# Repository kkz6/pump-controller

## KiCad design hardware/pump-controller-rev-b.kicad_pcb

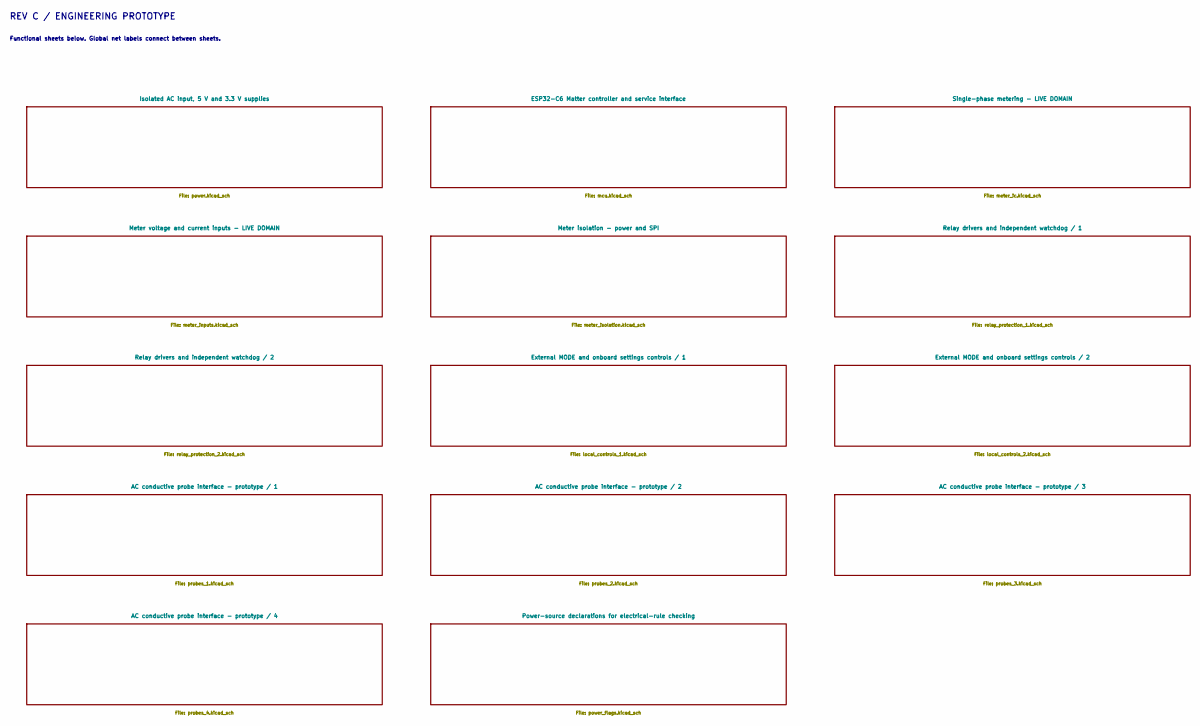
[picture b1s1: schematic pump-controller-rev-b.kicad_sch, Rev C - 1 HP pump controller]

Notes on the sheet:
REV C / ENGINEERING PROTOTYPE
Functional sheets below. Global net labels connect between sheets.

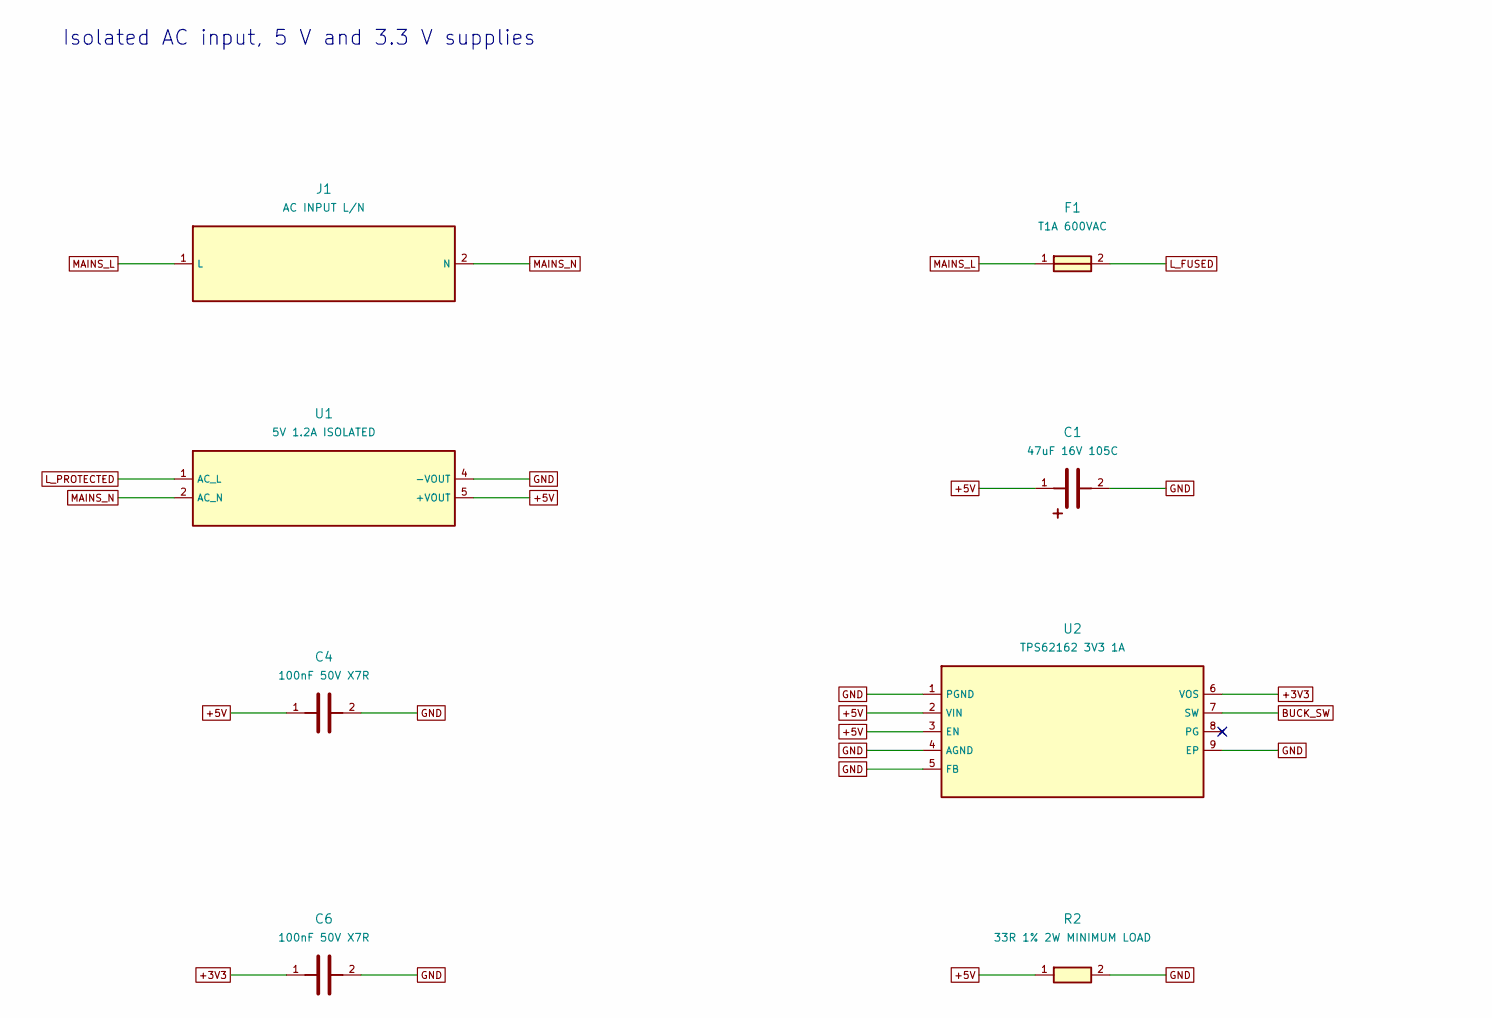
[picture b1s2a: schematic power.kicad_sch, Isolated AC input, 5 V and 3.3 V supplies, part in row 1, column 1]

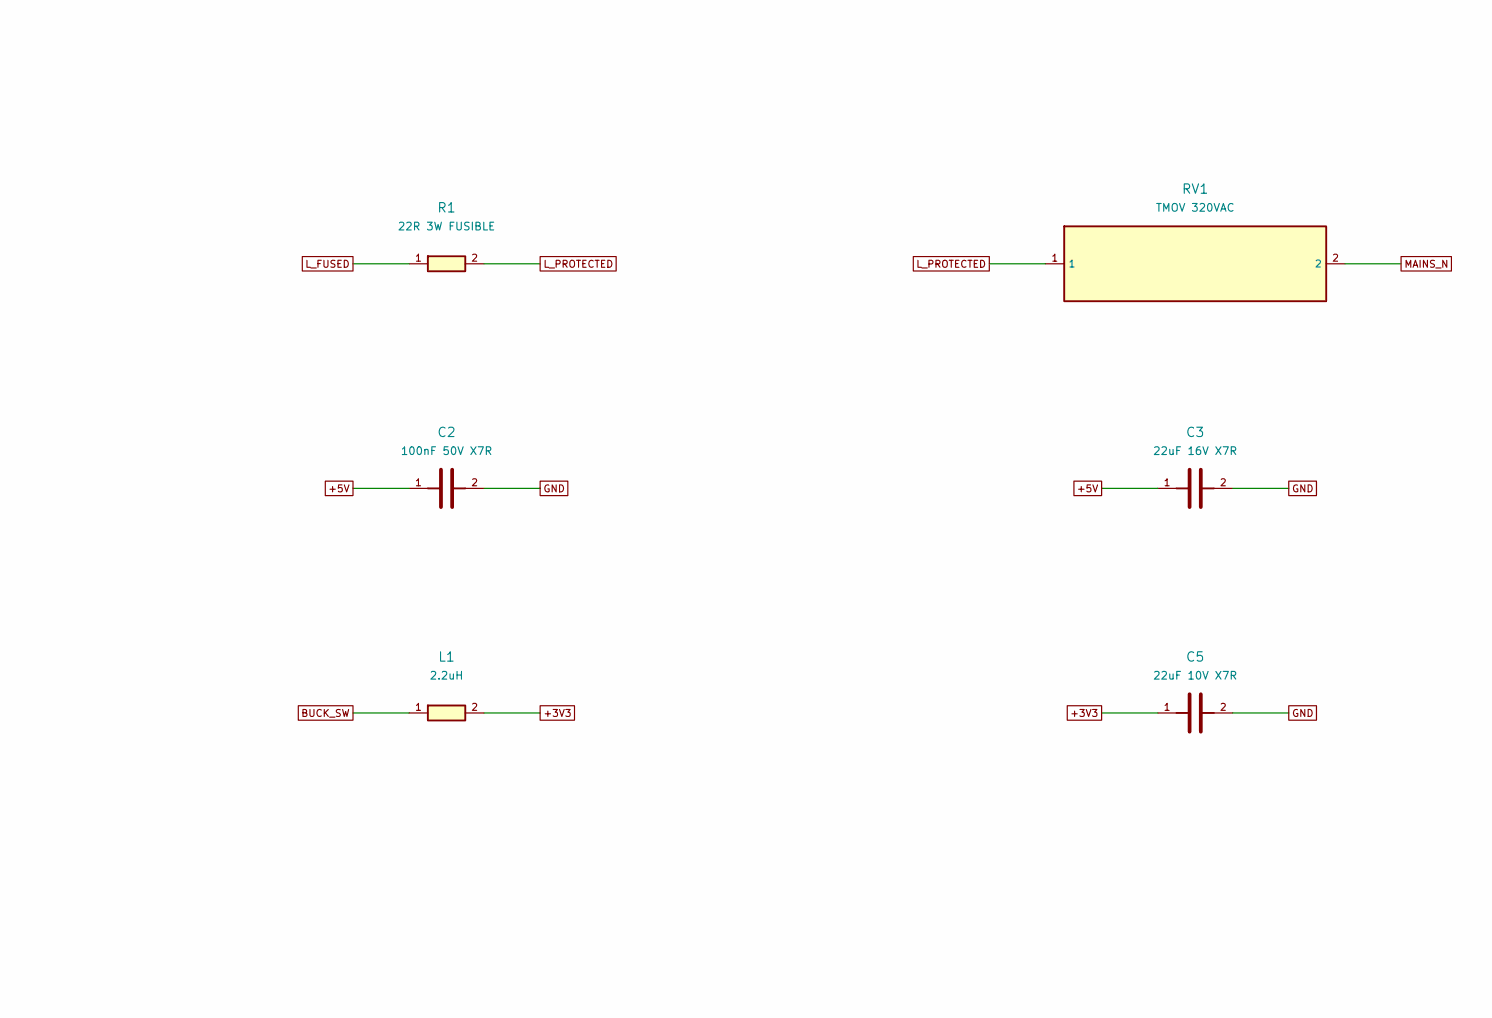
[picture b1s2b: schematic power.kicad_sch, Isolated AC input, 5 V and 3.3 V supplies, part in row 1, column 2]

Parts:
C1: 47uF 16V 105C; CP_Radial_D5.0mm_P2.00mm; MPN Generic 47uF 16V 105C low-impedance ele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
C2, C4, C6: 100nF 50V X7R; C_0805_2012Metric; MPN Generic 100nF 50V X7R 0805
C3: 22uF 16V X7R; C_1210_3225Metric; MPN Generic 22uF 16V X7R 1210
C5: 22uF 10V X7R; C_1210_3225Metric; MPN Generic 22uF 10V X7R 1210
F1: T1A 600VAC; Fuse_Axial_5x20_P27.94; MPN 0ADKP1000-RE
J1: AC INPUT L/N; TerminalBlock_Phoenix_MKDS-1,5-2-5.08_1x02_P5.08mm_Horizont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; MPN 1715721
L1: 2.2uH; L_Wuerth_MAPI-4030; MPN 74438357022
R1: 22R 3W FUSIBLE; R_Axial_L13_D6_P20.32; MPN AC03000002209JACCS
R2: 33R 1% 2W MINIMUM LOAD; R_2512_6332Metric; MPN CRM2512-FX-33R0ELF
RV1: TMOV 320VAC; TMOV14_Inline_P7.5; MPN TMOV14RP320EL2B7
U1: 5V 1.2A ISOLATED; RACM06E; MPN RACM06E-05SK/277
U2: TPS62162 3V3 1A; Texas_DSG0008A_WSON-8-1EP_2x2mm_P0.5mm_EP0.9x1.6mm_ThermalV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; MPN TPS62162DSGR

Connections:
+3V3: C5.1, C6.1, L1.2, U2.6 (VOS); also elsewhere on the board
+5V: C1.1, C2.1, C3.1, C4.1, R2.1, U1.5 (+VOUT), U2.2 (VIN), U2.3 (EN); also elsewhere on the board
BUCK_SW: L1.1, U2.7 (SW)
GND: C1.2, C2.2, C3.2, C4.2, C5.2, C6.2, R2.2, U1.4 (-VOUT), U2.1 (PGND), U2.4 (AGND), U2.5 (FB), U2.9 (EP); also elsewhere on the board
L_FUSED: F1.2, R1.1
L_PROTECTED: R1.2, RV1.1, U1.1 (AC_L); also elsewhere on the board
MAINS_L: F1.1, J1.1 (L)
MAINS_N: J1.2 (N), RV1.2, U1.2 (AC_N); also elsewhere on the board

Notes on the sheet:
Isolated AC input, 5 V and 3.3 V supplies

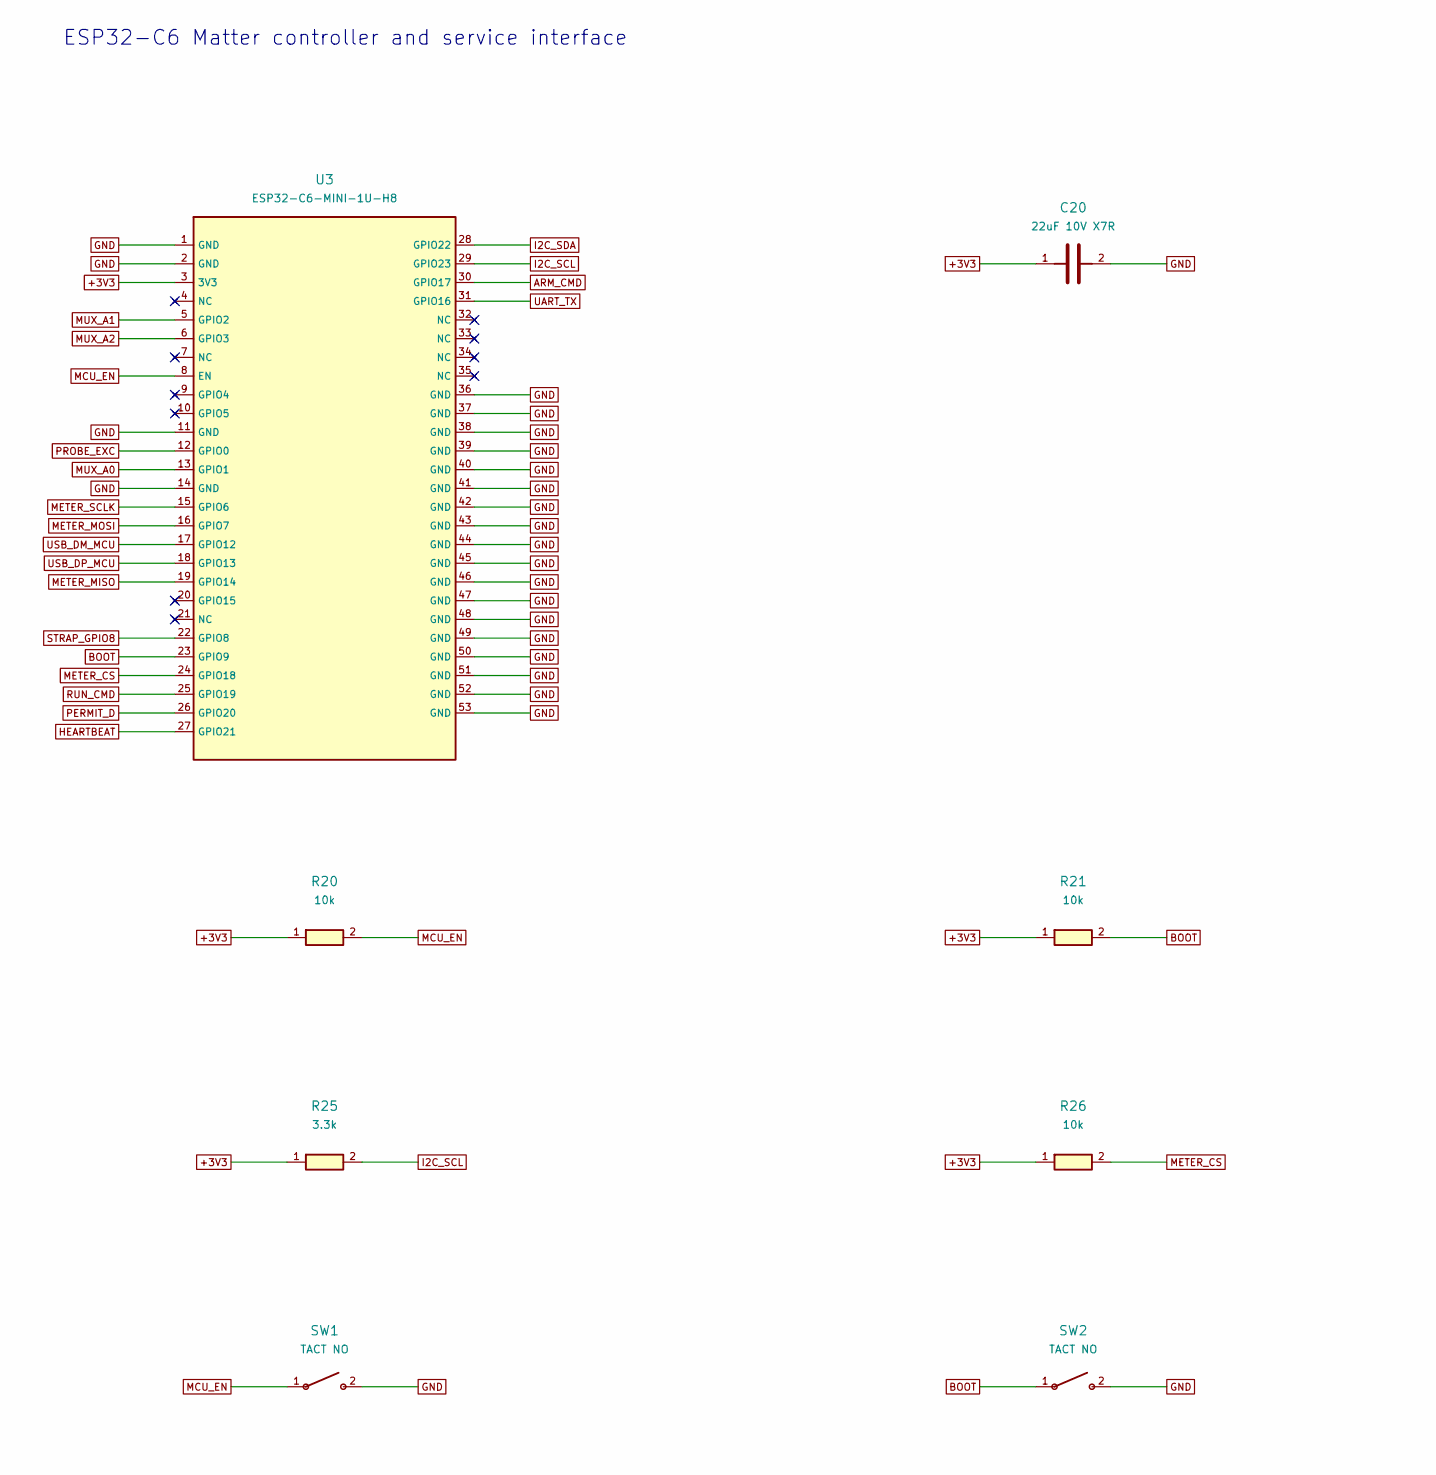
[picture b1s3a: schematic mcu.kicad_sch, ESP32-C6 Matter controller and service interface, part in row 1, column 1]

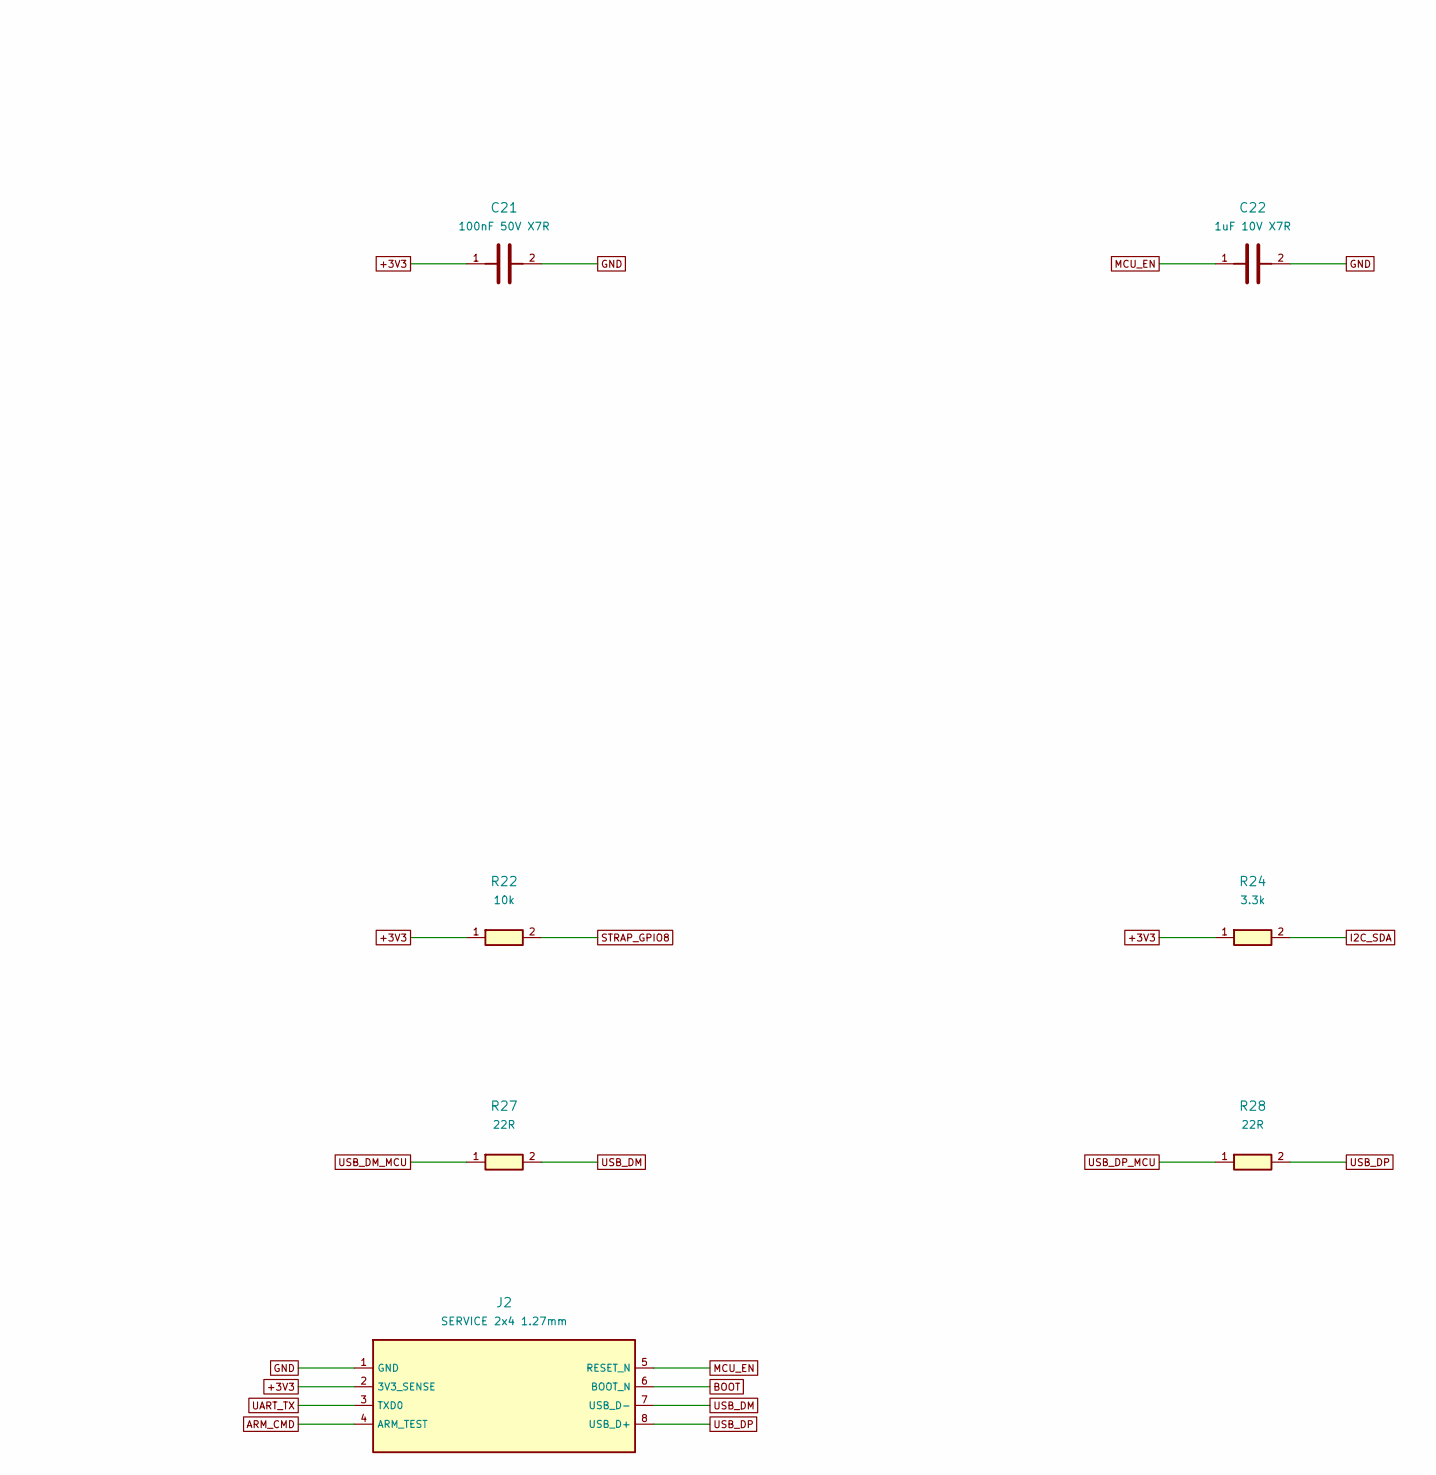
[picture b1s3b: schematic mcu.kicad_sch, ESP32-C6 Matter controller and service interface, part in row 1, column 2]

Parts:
C20: 22uF 10V X7R; C_1210_3225Metric; MPN Generic 22uF 10V X7R 1210
C21: 100nF 50V X7R; C_0805_2012Metric; MPN Generic 100nF 50V X7R 0805
C22: 1uF 10V X7R; C_0805_2012Metric; MPN Generic 1uF 10V X7R 0805
J2: SERVICE 2x4 1.27mm; PinHeader_2x04_P1.27mm_Vertical; MPN Generic 2x4 1.27 mm vertical male header
R20, R21, R22, R26: 10k; R_0805_2012Metric; MPN Generic 10k 1% 0.125 W 0805
R24, R25: 3.3k; R_0805_2012Metric; MPN Generic 3.3k 1% 0.125 W 0805
R27, R28: 22R; R_0805_2012Metric; MPN Generic 22R 1% 0.125 W 0805
SW1, SW2: TACT NO; SW_SPST_TL3305A; MPN TL3305AF160QG
U3: ESP32-C6-MINI-1U-H8; ESP32-C6-MINI-1U; MPN ESP32-C6-MINI-1U-H8

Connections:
+3V3: C20.1, C21.1, J2.2 (3V3_SENSE), R20.1, R21.1, R22.1, R24.1, R25.1, R26.1, U3.3 (3V3); also elsewhere on the board
ARM_CMD: J2.4 (ARM_TEST), U3.30 (GPIO17); also elsewhere on the board
BOOT: J2.6 (BOOT_N), R21.2, SW2.1, U3.23 (GPIO9)
GND: C20.2, C21.2, C22.2, J2.1 (GND), SW1.2, SW2.2, U3.1 (GND), U3.2 (GND), U3.11 (GND), U3.14 (GND), U3.36 (GND), U3.37 (GND), U3.38 (GND), U3.39 (GND), U3.40 (GND), U3.41 (GND), U3.42 (GND), U3.43 (GND), U3.44 (GND), U3.45 (GND), U3.46 (GND), U3.47 (GND), U3.48 (GND), U3.49 (GND), U3.50 (GND), U3.51 (GND), U3.52 (GND), U3.53 (GND); also elsewhere on the board
HEARTBEAT: U3.27 (GPIO21); also elsewhere on the board
I2C_SCL: R25.2, U3.29 (GPIO23); also elsewhere on the board
I2C_SDA: R24.2, U3.28 (GPIO22); also elsewhere on the board
MCU_EN: C22.1, J2.5 (RESET_N), R20.2, SW1.1, U3.8 (EN); also elsewhere on the board
METER_CS: R26.2, U3.24 (GPIO18); also elsewhere on the board
METER_MISO: U3.19 (GPIO14); also elsewhere on the board
METER_MOSI: U3.16 (GPIO7); also elsewhere on the board
METER_SCLK: U3.15 (GPIO6); also elsewhere on the board
MUX_A0: U3.13 (GPIO1); also elsewhere on the board
MUX_A1: U3.5 (GPIO2); also elsewhere on the board
MUX_A2: U3.6 (GPIO3); also elsewhere on the board
PERMIT_D: U3.26 (GPIO20); also elsewhere on the board
PROBE_EXC: U3.12 (GPIO0); also elsewhere on the board
RUN_CMD: U3.25 (GPIO19); also elsewhere on the board
STRAP_GPIO8: R22.2, U3.22 (GPIO8)
UART_TX: J2.3 (TXD0), U3.31 (GPIO16)
USB_DM: J2.7 (USB_D-), R27.2
USB_DM_MCU: R27.1, U3.17 (GPIO12)
USB_DP: J2.8 (USB_D+), R28.2
USB_DP_MCU: R28.1, U3.18 (GPIO13)

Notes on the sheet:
ESP32-C6 Matter controller and service interface

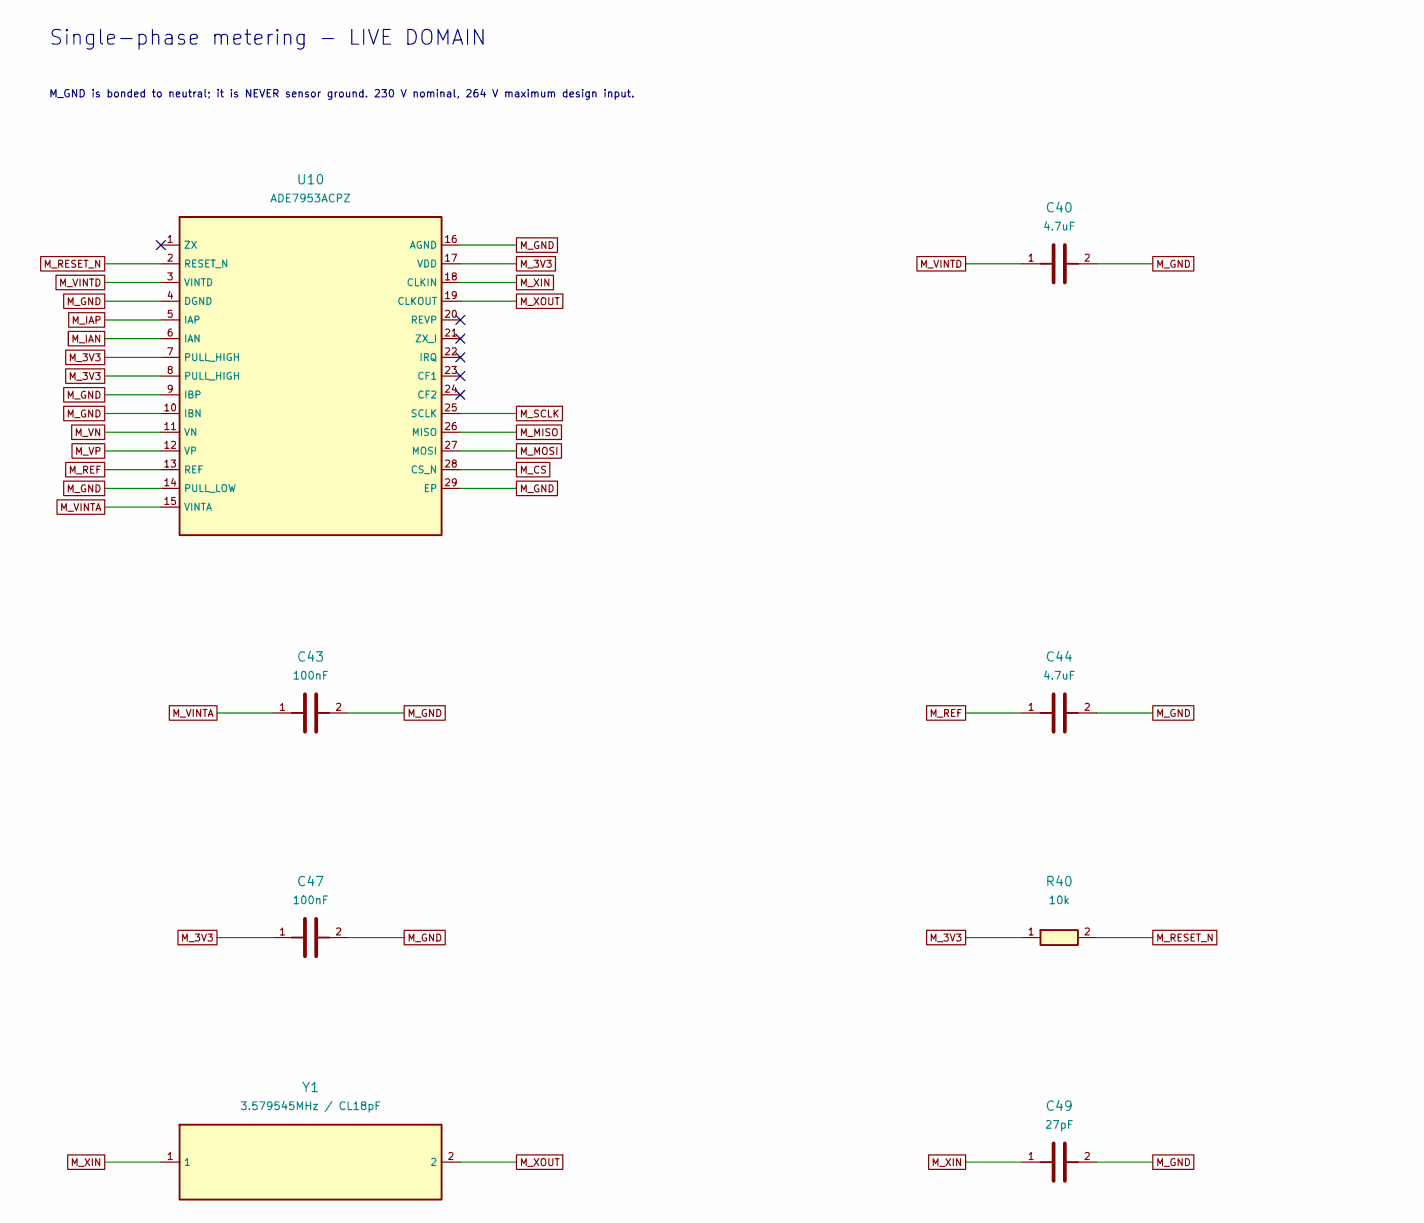
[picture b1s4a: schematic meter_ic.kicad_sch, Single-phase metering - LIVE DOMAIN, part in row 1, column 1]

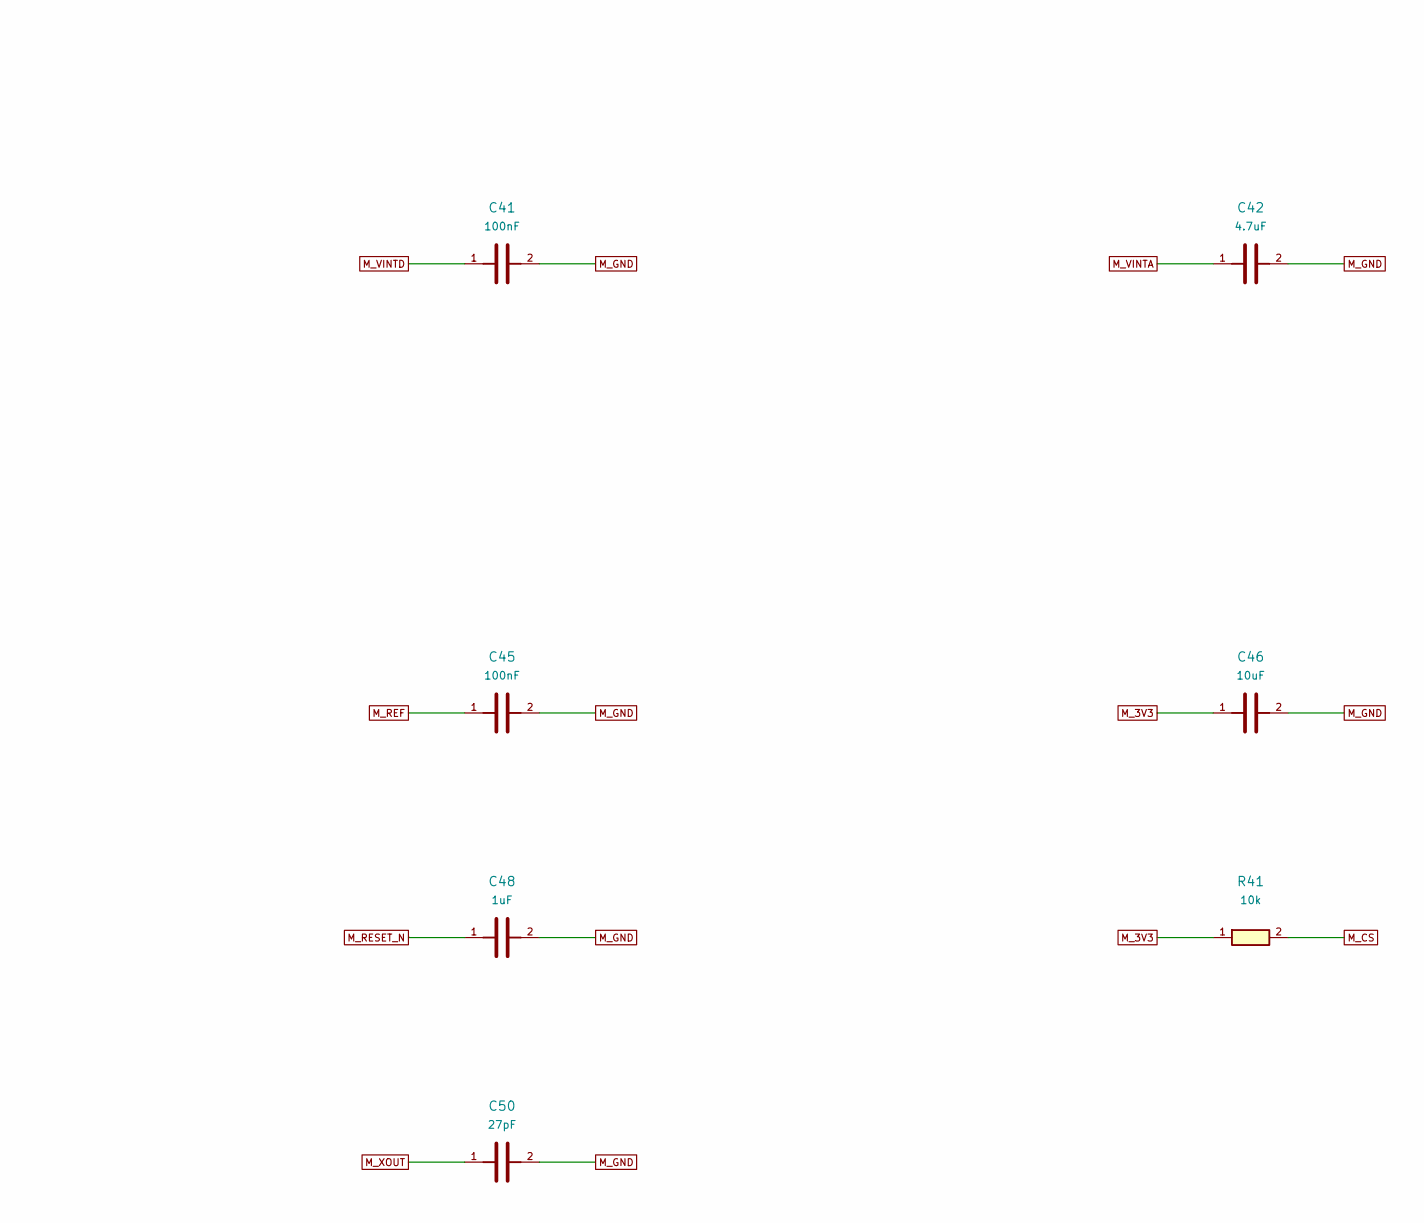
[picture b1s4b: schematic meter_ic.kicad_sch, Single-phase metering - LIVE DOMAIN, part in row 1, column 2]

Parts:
C40, C42, C44: 4.7uF; C_0805_2012Metric; MPN SPEC: 4.7uF X7R, 10%, 16V
C41, C43, C45, C47: 100nF; C_0603_1608Metric; MPN SPEC: 100nF X7R, 10%, 16V
C46: 10uF; C_0805_2012Metric; MPN SPEC: 10uF X7R, 10%, 16V
C48: 1uF; C_0603_1608Metric; MPN SPEC: 1uF X7R, 10%, 16V
C49, C50: 27pF; C_0603_1608Metric; MPN SPEC: 27pF C0G, 5%, 50V
R40, R41: 10k; R_0603_1608Metric; MPN SPEC: 10k 1%, 0.1W, 0603
U10: ADE7953ACPZ; LFCSP-28-1EP_5x5mm_P0.5mm_EP3.14x3.14mm; MPN ADE7953ACPZ
Y1: 3.579545MHz / CL18pF; Crystal_SMD_HC49-SD; MPN ABLS-3.579545MHZ-B2-T

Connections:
M_3V3: C46.1, C47.1, R40.1, R41.1, U10.7 (PULL_HIGH), U10.8 (PULL_HIGH), U10.17 (VDD); also elsewhere on the board
M_CS: R41.2, U10.28 (CS_N); also elsewhere on the board
M_GND: C40.2, C41.2, C42.2, C43.2, C44.2, C45.2, C46.2, C47.2, C48.2, C49.2, C50.2, U10.4 (DGND), U10.9 (IBP), U10.10 (IBN), U10.14 (PULL_LOW), U10.16 (AGND), U10.29 (EP); also elsewhere on the board
M_IAN: U10.6 (IAN); also elsewhere on the board
M_IAP: U10.5 (IAP); also elsewhere on the board
M_MISO: U10.26 (MISO); also elsewhere on the board
M_MOSI: U10.27 (MOSI); also elsewhere on the board
M_REF: C44.1, C45.1, U10.13 (REF)
M_RESET_N: C48.1, R40.2, U10.2 (RESET_N)
M_SCLK: U10.25 (SCLK); also elsewhere on the board
M_VINTA: C42.1, C43.1, U10.15 (VINTA)
M_VINTD: C40.1, C41.1, U10.3 (VINTD)
M_VN: U10.11 (VN); also elsewhere on the board
M_VP: U10.12 (VP); also elsewhere on the board
M_XIN: C49.1, U10.18 (CLKIN), Y1.1
M_XOUT: C50.1, U10.19 (CLKOUT), Y1.2

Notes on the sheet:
Single-phase metering - LIVE DOMAIN
M_GND is bonded to neutral; it is NEVER sensor ground. 230 V nominal, 264 V maximum design input.

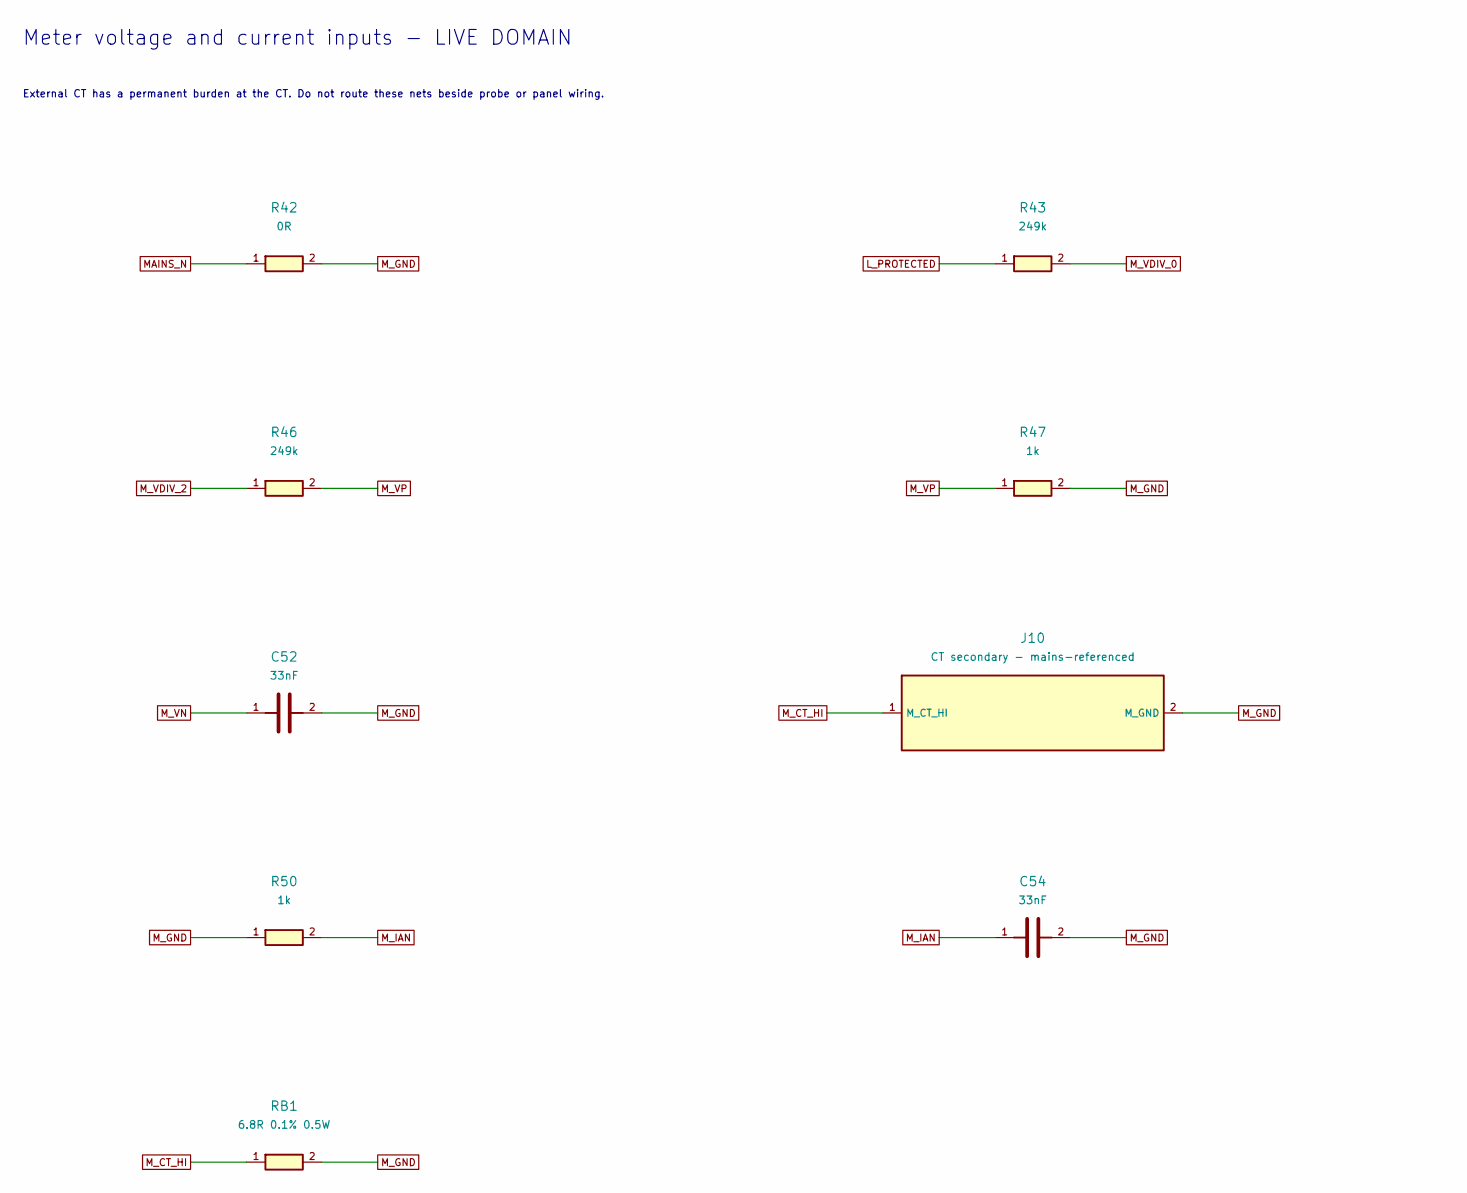
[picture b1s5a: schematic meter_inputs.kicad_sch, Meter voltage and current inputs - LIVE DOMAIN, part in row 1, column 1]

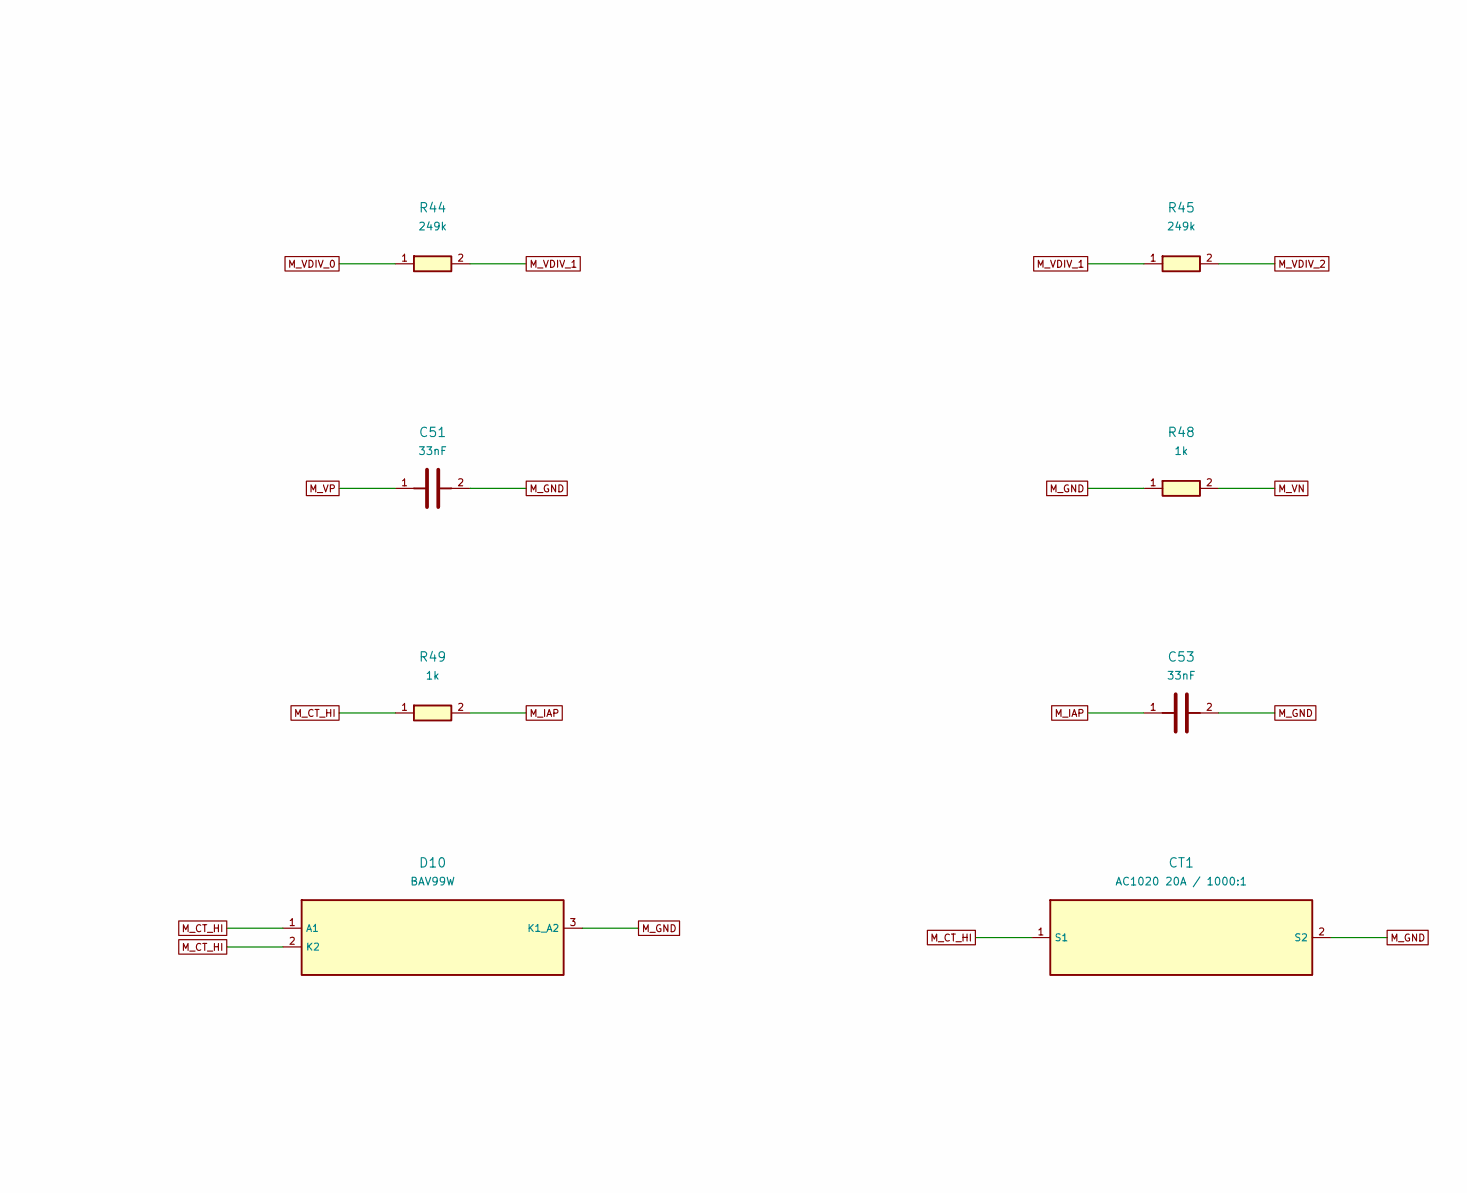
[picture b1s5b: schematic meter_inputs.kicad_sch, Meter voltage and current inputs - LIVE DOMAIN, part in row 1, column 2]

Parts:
C51, C52, C53, C54: 33nF; C_0603_1608Metric; MPN SPEC: 33nF C0G, 5%, 50V
CT1: AC1020 20A / 1000:1; MPN AC1020
D10: BAV99W; SOT-323_SC-70; MPN BAV99W,115
J10: CT secondary - mains-referenced; PhoenixContact_MC_1,5_2-G-3.81_1x02_P3.81mm_Horizontal; MPN Phoenix MC 1,5/2-G-3,81
R42: 0R; R_0603_1608Metric; MPN RC0603JR-070RL
R43, R44, R45, R46: 249k; R_1206_3216Metric; MPN TNPW1206249KBEEA
R47: 1k; R_0603_1608Metric; MPN RT0603BRD071KL
R48, R49, R50: 1k; R_0603_1608Metric; MPN SPEC: 1k 1%, 0.1W, 0603
RB1: 6.8R 0.1% 0.5W; MPN SPEC: 6.8 ohm 0.1% metal film 0.5W

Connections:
L_PROTECTED: R43.1; also elsewhere on the board
MAINS_N: R42.1; also elsewhere on the board
M_CT_HI: CT1.1 (S1), D10.1 (A1), D10.2 (K2), J10.1 (M_CT_HI), R49.1, RB1.1
M_GND: C51.2, C52.2, C53.2, C54.2, CT1.2 (S2), D10.3 (K1_A2), J10.2 (M_GND), R42.2, R47.2, R48.1, R50.1, RB1.2; also elsewhere on the board
M_IAN: C54.1, R50.2; also elsewhere on the board
M_IAP: C53.1, R49.2; also elsewhere on the board
M_VDIV_0: R43.2, R44.1
M_VDIV_1: R44.2, R45.1
M_VDIV_2: R45.2, R46.1
M_VN: C52.1, R48.2; also elsewhere on the board
M_VP: C51.1, R46.2, R47.1; also elsewhere on the board

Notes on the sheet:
Meter voltage and current inputs - LIVE DOMAIN
External CT has a permanent burden at the CT. Do not route these nets beside probe or panel wiring.
